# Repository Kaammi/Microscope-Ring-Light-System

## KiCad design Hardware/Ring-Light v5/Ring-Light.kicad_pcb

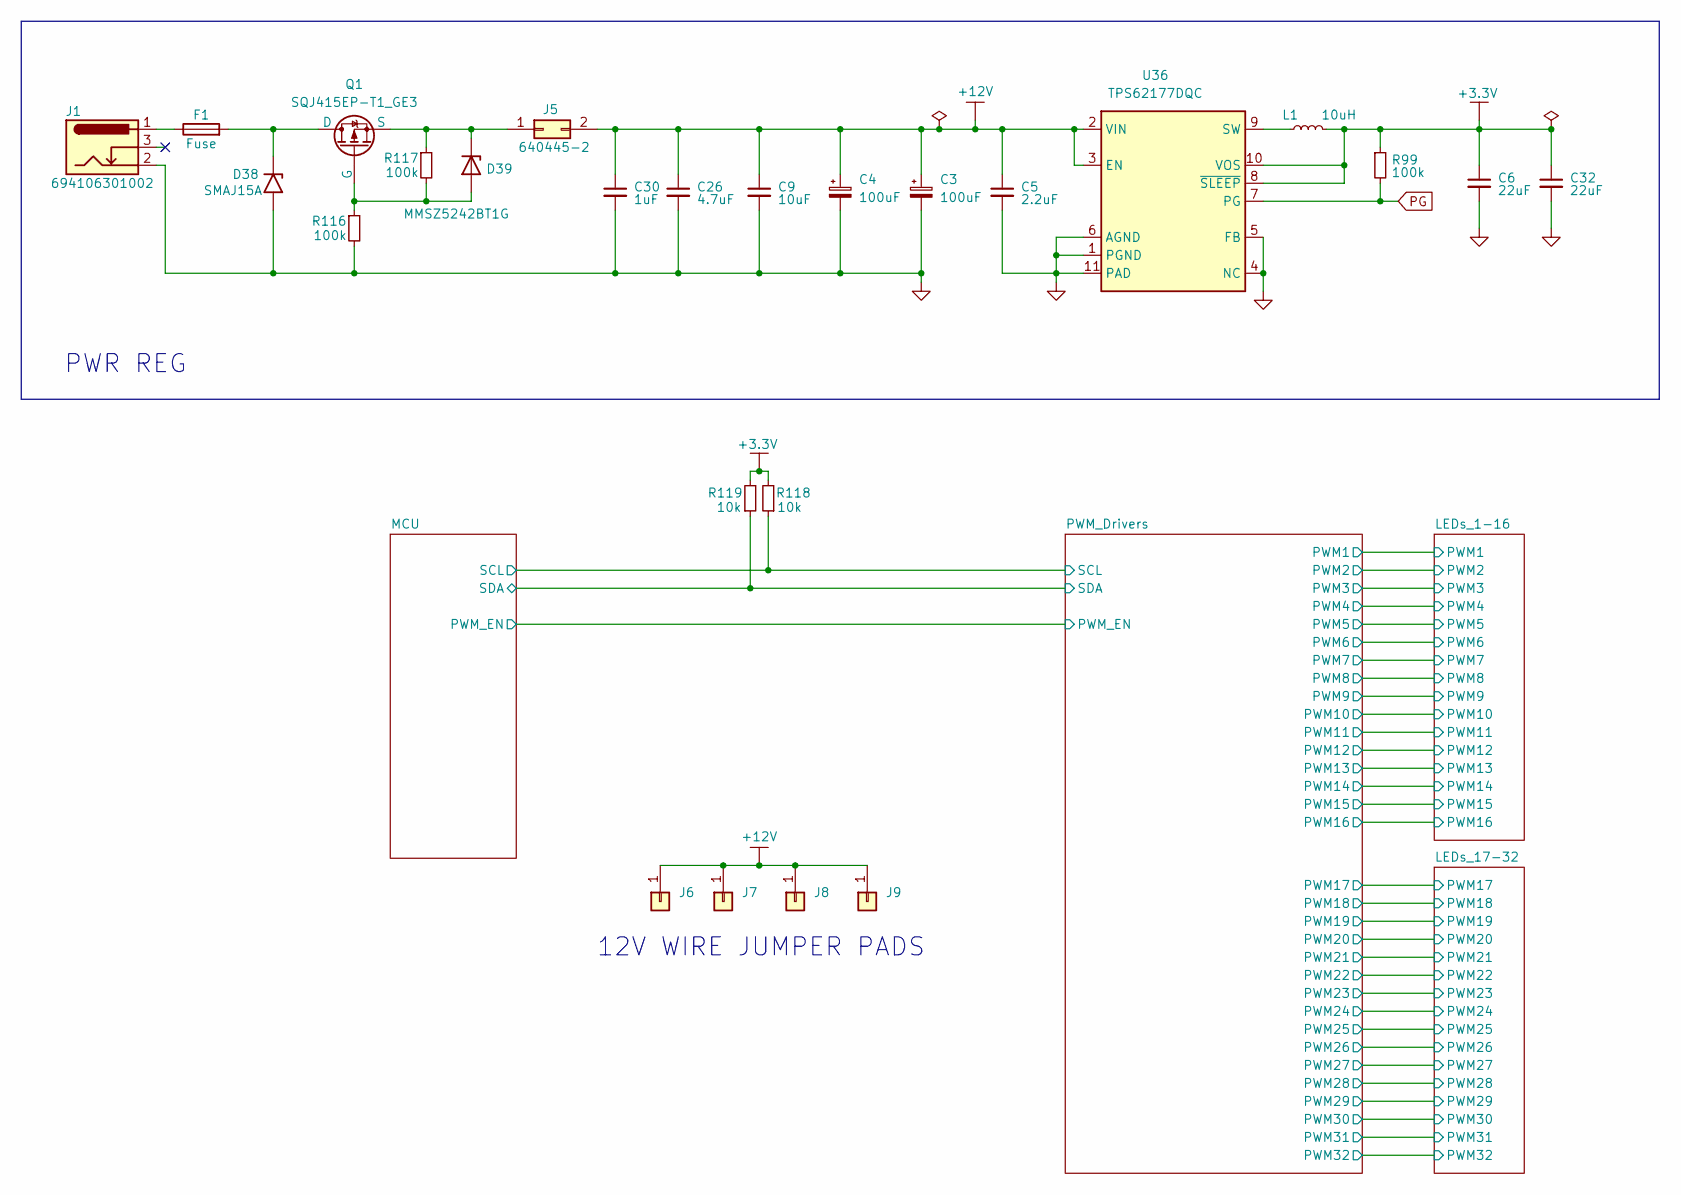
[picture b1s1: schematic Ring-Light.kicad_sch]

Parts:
C3, C4: 100uF
C5: 2.2uF; C_0805_2012Metric
C6, C32: 22uF; C_0805_2012Metric
C9: 10uF; C_0805_2012Metric
C26: 4.7uF; C_0805_2012Metric
C30: 1uF; C_0805_2012Metric
D38: SMAJ15A; D_SMA
D39: MMSZ5242BT1G; SOD3716X135N
F1: Fuse
J1: 694106301002
J5: 640445-2
J6, J7, J8, J9: Conn_01x01
L1: 10uH; WE-LHMI_4020
Q1: SQJ415EP-T1_GE3; SOT_SQJ415EP_VIS
R99, R116, R117: 100k; R_0402_1005Metric
R118, R119: 10k; R_0402_1005Metric
U36: TPS62177DQC; WSON-10-1EP_2x3mm_P0.5mm_EP0.84x2.4mm_ThermalVias

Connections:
+3.3V: C6.1, C32.1, L1.2, R99.1, R118.2, R119.2, U36.8 (~SLEEP), U36.10 (VOS); also elsewhere on the board
+12V: C3.1, C4.1, C5.1, C9.1, C26.1, C30.1, J5.2, J6.1 (Pin_1_1), J7.1 (Pin_1_1), J8.1 (Pin_1_1), J9.1 (Pin_1_1), U36.2 (VIN), U36.3 (EN); also elsewhere on the board
/MCU/SCL: R118.1; also elsewhere on the board
/MCU/SDA: R119.1; also elsewhere on the board
GND: C3.2, C4.2, C5.2, C6.2, C9.2, C26.2, C30.2, C32.2, D38.2 (A2), J1.2, R116.2, U36.1 (PGND), U36.4 (NC), U36.5 (FB), U36.6 (AGND), U36.11 (PAD); also elsewhere on the board
unnamed: D38.1 (A1), F1.2, Q1.5 (D)
unnamed: D39.2 (A), Q1.4 (G), R116.1, R117.2
unnamed: D39.1 (K), J5.1, Q1.1 (S), Q1.2 (S), Q1.3 (S), R117.1
unnamed: F1.1, J1.1
unnamed: L1.1, U36.9 (SW)
PG: R99.2, U36.7 (PG)

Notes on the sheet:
PWR REG
12V WIRE JUMPER PADS

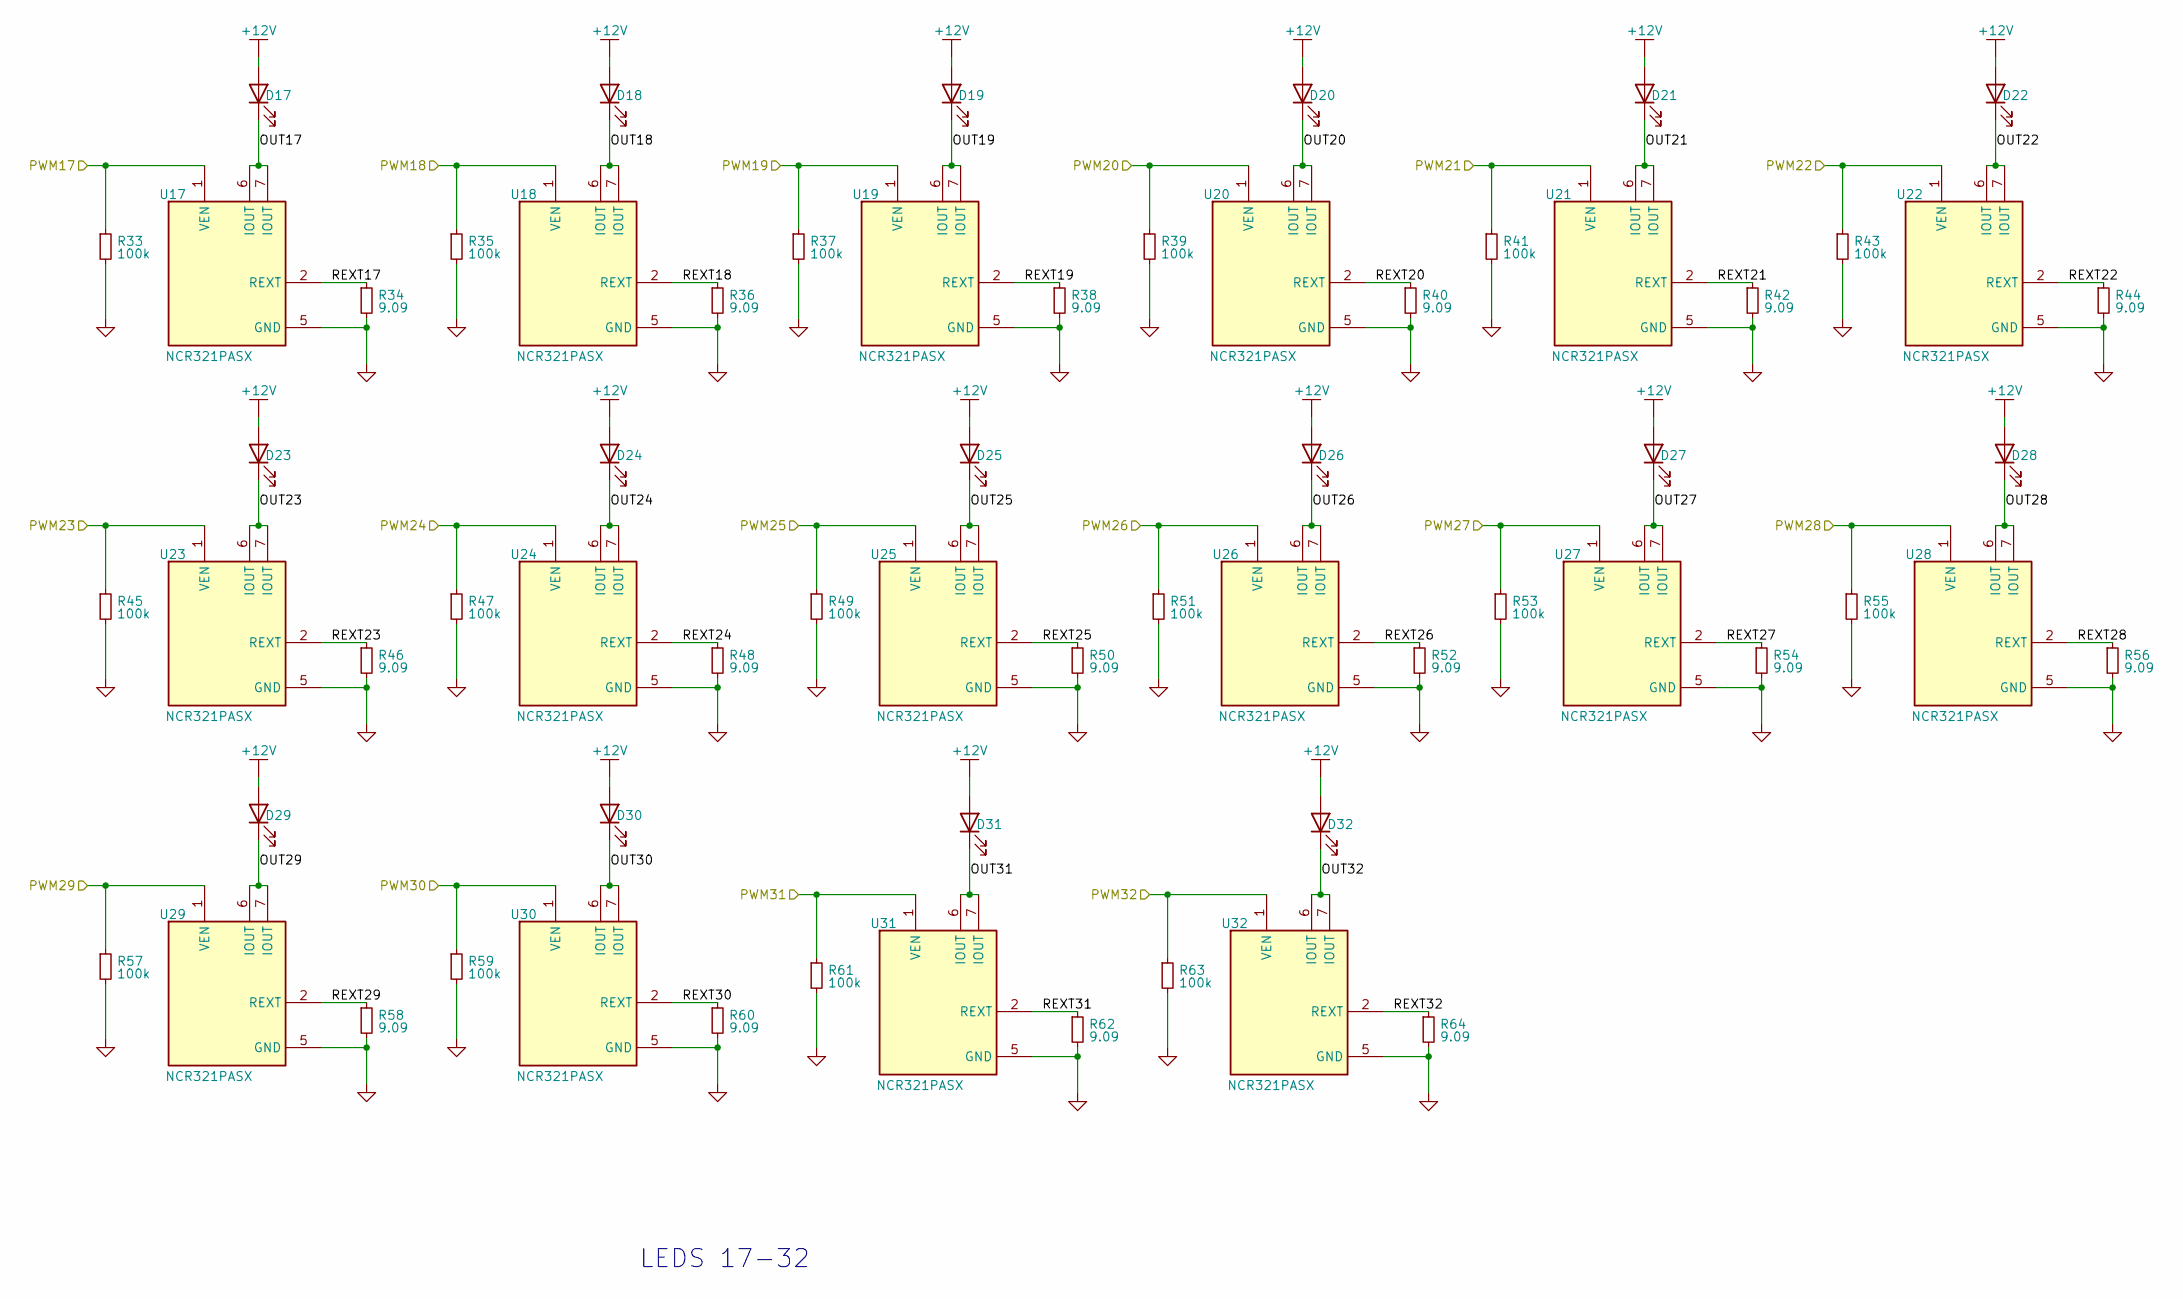
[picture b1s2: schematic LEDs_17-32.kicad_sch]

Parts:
D17, D18, D19, D20, D21, D22, D23, D24, D25, D26, D27, D28, D29, D30, D31, D32: LED; GWJTLRS1EMLVL5XX531
R33, R35, R37, R39, R41, R43, R45, R47, R49, R51, R53, R55, R57, R59, R61, R63: 100k; R_0402_1005Metric
R34, R36, R38, R40, R42, R44, R46, R48, R50, R52, R54, R56, R58, R60, R62, R64: 9.09; R_0402_1005Metric
U17, U18, U19, U20, U21, U22, U23, U24, U25, U26, U27, U28, U29, U30, U31, U32: NCR321PASX; Manufacturer_Part_Number NCR321PASX; Mouser Part Number 771-NCR321PASX

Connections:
+12V: D17.3 (A), D17.4 (A), D18.3 (A), D18.4 (A), D19.3 (A), D19.4 (A), D20.3 (A), D20.4 (A), D21.3 (A), D21.4 (A), D22.3 (A), D22.4 (A), D23.3 (A), D23.4 (A), D24.3 (A), D24.4 (A), D25.3 (A), D25.4 (A), D26.3 (A), D26.4 (A), D27.3 (A), D27.4 (A), D28.3 (A), D28.4 (A), D29.3 (A), D29.4 (A), D30.3 (A), D30.4 (A), D31.3 (A), D31.4 (A), D32.3 (A), D32.4 (A); also elsewhere on the board
/LEDs_17-32/OUT17: D17.1 (K), D17.2 (K), U17.6 (IOUT), U17.7 (IOUT)
/LEDs_17-32/OUT18: D18.1 (K), D18.2 (K), U18.6 (IOUT), U18.7 (IOUT)
/LEDs_17-32/OUT19: D19.1 (K), D19.2 (K), U19.6 (IOUT), U19.7 (IOUT)
/LEDs_17-32/OUT20: D20.1 (K), D20.2 (K), U20.6 (IOUT), U20.7 (IOUT)
/LEDs_17-32/OUT21: D21.1 (K), D21.2 (K), U21.6 (IOUT), U21.7 (IOUT)
/LEDs_17-32/OUT22: D22.1 (K), D22.2 (K), U22.6 (IOUT), U22.7 (IOUT)
/LEDs_17-32/OUT23: D23.1 (K), D23.2 (K), U23.6 (IOUT), U23.7 (IOUT)
/LEDs_17-32/OUT24: D24.1 (K), D24.2 (K), U24.6 (IOUT), U24.7 (IOUT)
/LEDs_17-32/OUT25: D25.1 (K), D25.2 (K), U25.6 (IOUT), U25.7 (IOUT)
/LEDs_17-32/OUT26: D26.1 (K), D26.2 (K), U26.6 (IOUT), U26.7 (IOUT)
/LEDs_17-32/OUT27: D27.1 (K), D27.2 (K), U27.6 (IOUT), U27.7 (IOUT)
/LEDs_17-32/OUT28: D28.1 (K), D28.2 (K), U28.6 (IOUT), U28.7 (IOUT)
/LEDs_17-32/OUT29: D29.1 (K), D29.2 (K), U29.6 (IOUT), U29.7 (IOUT)
/LEDs_17-32/OUT30: D30.1 (K), D30.2 (K), U30.6 (IOUT), U30.7 (IOUT)
/LEDs_17-32/OUT31: D31.1 (K), D31.2 (K), U31.6 (IOUT), U31.7 (IOUT)
/LEDs_17-32/OUT32: D32.1 (K), D32.2 (K), U32.6 (IOUT), U32.7 (IOUT)
/LEDs_17-32/PWM17: R33.1, U17.1 (VEN); also elsewhere on the board
/LEDs_17-32/PWM18: R35.1, U18.1 (VEN); also elsewhere on the board
/LEDs_17-32/PWM19: R37.1, U19.1 (VEN); also elsewhere on the board
/LEDs_17-32/PWM20: R39.1, U20.1 (VEN); also elsewhere on the board
/LEDs_17-32/PWM21: R41.1, U21.1 (VEN); also elsewhere on the board
/LEDs_17-32/PWM22: R43.1, U22.1 (VEN); also elsewhere on the board
/LEDs_17-32/PWM23: R45.1, U23.1 (VEN); also elsewhere on the board
/LEDs_17-32/PWM24: R47.1, U24.1 (VEN); also elsewhere on the board
/LEDs_17-32/PWM25: R49.1, U25.1 (VEN); also elsewhere on the board
/LEDs_17-32/PWM26: R51.1, U26.1 (VEN); also elsewhere on the board
/LEDs_17-32/PWM27: R53.1, U27.1 (VEN); also elsewhere on the board
/LEDs_17-32/PWM28: R55.1, U28.1 (VEN); also elsewhere on the board
/LEDs_17-32/PWM29: R57.1, U29.1 (VEN); also elsewhere on the board
/LEDs_17-32/PWM30: R59.1, U30.1 (VEN); also elsewhere on the board
/LEDs_17-32/PWM31: R61.1, U31.1 (VEN); also elsewhere on the board
/LEDs_17-32/PWM32: R63.1, U32.1 (VEN); also elsewhere on the board
/LEDs_17-32/REXT17: R34.1, U17.2 (REXT)
/LEDs_17-32/REXT18: R36.1, U18.2 (REXT)
/LEDs_17-32/REXT19: R38.1, U19.2 (REXT)
/LEDs_17-32/REXT20: R40.1, U20.2 (REXT)
/LEDs_17-32/REXT21: R42.1, U21.2 (REXT)
/LEDs_17-32/REXT22: R44.1, U22.2 (REXT)
/LEDs_17-32/REXT23: R46.1, U23.2 (REXT)
/LEDs_17-32/REXT24: R48.1, U24.2 (REXT)
/LEDs_17-32/REXT25: R50.1, U25.2 (REXT)
/LEDs_17-32/REXT26: R52.1, U26.2 (REXT)
/LEDs_17-32/REXT27: R54.1, U27.2 (REXT)
/LEDs_17-32/REXT28: R56.1, U28.2 (REXT)
/LEDs_17-32/REXT29: R58.1, U29.2 (REXT)
/LEDs_17-32/REXT30: R60.1, U30.2 (REXT)
/LEDs_17-32/REXT31: R62.1, U31.2 (REXT)
/LEDs_17-32/REXT32: R64.1, U32.2 (REXT)
GND: R33.2, R34.2, R35.2, R36.2, R37.2, R38.2, R39.2, R40.2, R41.2, R42.2, R43.2, R44.2, R45.2, R46.2, R47.2, R48.2, R49.2, R50.2, R51.2, R52.2, R53.2, R54.2, R55.2, R56.2, R57.2, R58.2, R59.2, R60.2, R61.2, R62.2, R63.2, R64.2, U17.5 (GND), U18.5 (GND), U19.5 (GND), U20.5 (GND), U21.5 (GND), U22.5 (GND), U23.5 (GND), U24.5 (GND), U25.5 (GND), U26.5 (GND), U27.5 (GND), U28.5 (GND), U29.5 (GND), U30.5 (GND), U31.5 (GND), U32.5 (GND); also elsewhere on the board

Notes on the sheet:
LEDS 17-32

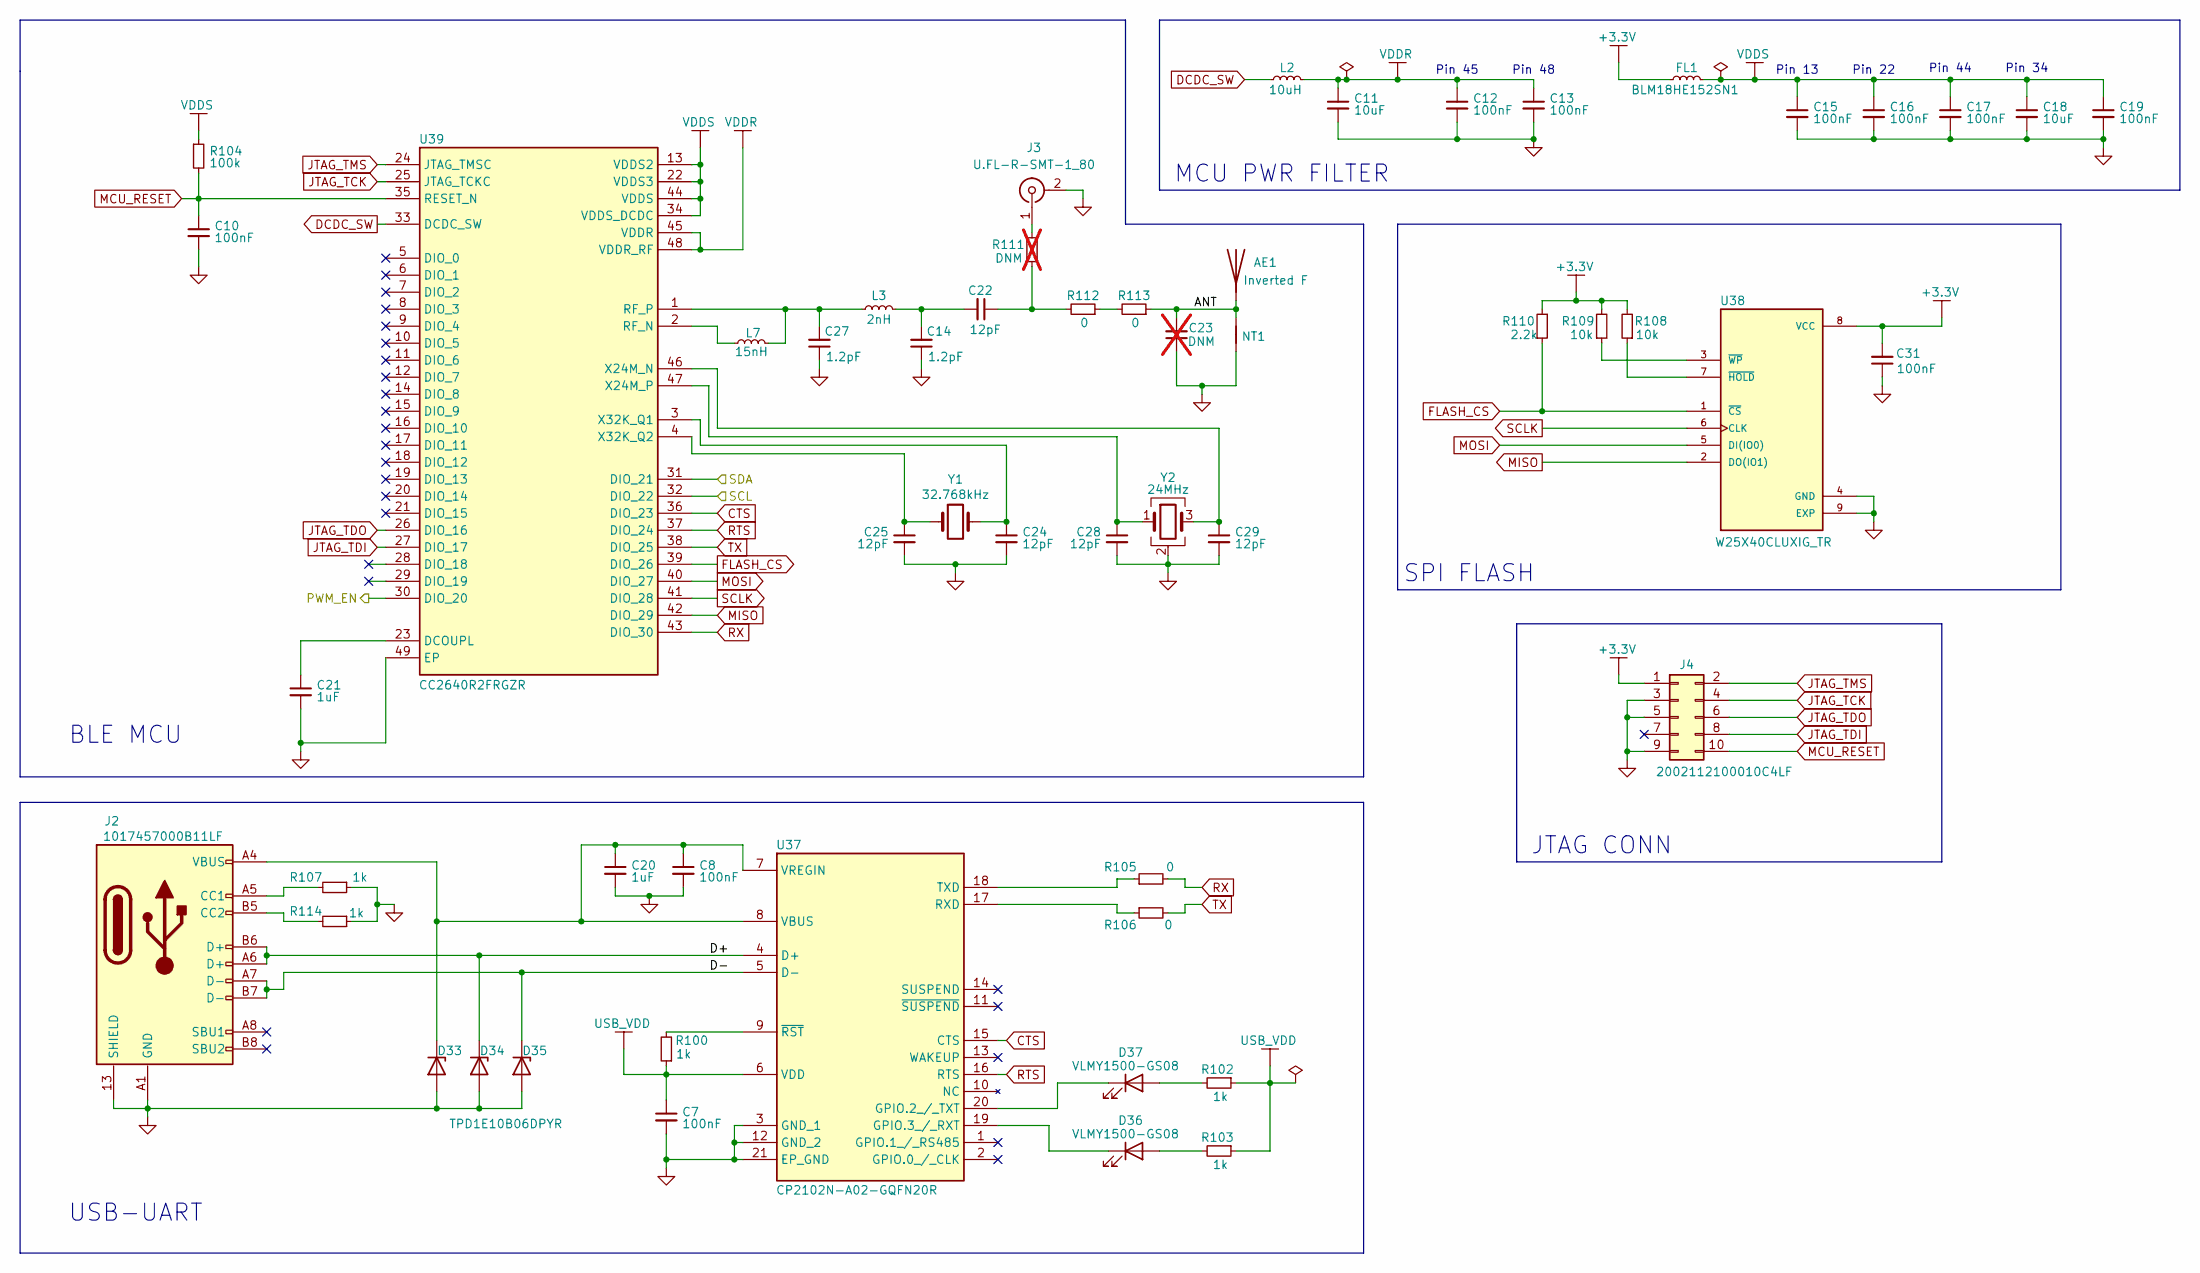
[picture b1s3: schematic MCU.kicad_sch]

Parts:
AE1: Inverted F
C7, C8, C10, C12, C13, C15, C16, C17, C19, C31: 100nF; C_0402_1005Metric
C11, C18: 10uF; C_0402_1005Metric
C14, C27: 1.2pF; C_0402_1005Metric
C20, C21: 1uF; C_0402_1005Metric
C22, C24, C25, C28, C29: 12pF; C_0402_1005Metric
C23: DNM; C_0402_1005Metric; not fitted
D33, D34, D35: TPD1E10B06DPYR; D_SOD-523
D36, D37: VLMY1500-GS08; LED_0402_1005Metric
FL1: BLM18HE152SN1; L_0603_1608Metric
J2: 1017457000B11LF
J3: U.FL-R-SMT-1_80; UFLRSMT180
J4: 2002112100010C4LF
L2: 10uH; L_0805_2012Metric
L3: 2nH
L7: 15nH
NT1: NetTie_2
R100, R102, R103, R107, R114: 1k; R_0402_1005Metric
R104: 100k; R_0402_1005Metric
R105, R106, R112, R113: 0; R_0402_1005Metric
R108, R109: 10k; R_0402_1005Metric
R110: 2.2k; R_0402_1005Metric
R111: DNM; R_0402_1005Metric; not fitted
U37: CP2102N-A02-GQFN20R; CP2102NA02GQFN20; Manufacturer_Part_Number CP2102N-A02-GQFN20R; Mouser Part Number 634-CP2102NA02QFN20R
U38: W25X40CLUXIG_TR; PSON50P300X200X60-9N; PARTREV F
U39: CC2640R2FRGZR; QFN50P700X700X100-49N-D; Manufacturer_Part_Number CC2640R2FRGZR; Mouser Part Number 595-CC2640R2FRGZR
Y1: 32.768kHz; FC135327680KAAG0
Y2: 24MHz; TSX-3225

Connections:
+3.3V: C31.2, FL1.1, J4.1, R108.2, R109.2, R110.2, U38.8 (VCC); also elsewhere on the board
/MCU/<NO NET>: C8.1, C20.1, D33.1 (K), J2.A4 (VBUS), J2.B4 (VBUS), U37.7 (VREGIN), U37.8 (VBUS)
/MCU/ANT: AE1.1, C23.2, NT1.2, R113.1
/MCU/D+: D34.1 (K), J2.A6 (D+), J2.B6 (D+), U37.4 (D+)
/MCU/D-: D35.1 (K), J2.A7 (D-), J2.B7 (D-), U37.5 (D-)
/MCU/PWM_EN: U39.30 (DIO_20); also elsewhere on the board
/MCU/SCL: U39.32 (DIO_22); also elsewhere on the board
/MCU/SDA: U39.31 (DIO_21); also elsewhere on the board
CTS: U37.15 (CTS), U39.36 (DIO_23)
DCDC_SW: L2.1, U39.33 (DCDC_SW)
FLASH_CS: R110.1, U38.1 (~CS), U39.39 (DIO_26)
GND: C7.2, C8.2, C10.2, C11.2, C12.2, C13.2, C14.1, C15.2, C16.2, C17.2, C18.2, C19.2, C20.2, C21.2, C23.1, C24.2, C25.2, C27.1, C28.2, C29.2, C31.1, D33.2 (A), D34.2 (A), D35.2 (A), J2.13 (SHIELD), J2.14 (SHIELD), J2.15 (SHIELD), J2.16 (SHIELD), J2.A1 (GND), J2.B1 (GND), J3.2 (Ext), J3.3 (Ext), J4.3, J4.5, J4.9, NT1.1, R107.1, R114.1, U37.3 (GND_1), U37.12 (GND_2), U37.21 (EP_GND), U38.4 (GND), U38.9 (EXP), U39.49 (EP), Y2.2 (G), Y2.4 (G); also elsewhere on the board
JTAG_TCK: J4.4, U39.25 (JTAG_TCKC)
JTAG_TDI: J4.8, U39.27 (DIO_17)
JTAG_TDO: J4.6, U39.26 (DIO_16)
JTAG_TMS: J4.2, U39.24 (JTAG_TMSC)
MCU_RESET: C10.1, J4.10, R104.2, U39.35 (RESET_N)
MISO: U38.2 (DO(IO1)), U39.42 (DIO_29)
MOSI: U38.5 (DI(IO0)), U39.40 (DIO_27)
unnamed: C14.2, C22.2, L3.2
unnamed: C22.1, R111.1, R112.2
unnamed: D36.2 (A), R103.2
unnamed: D36.1 (K), U37.19 (GPIO.3_/_RXT)
unnamed: D37.2 (A), R102.2
unnamed: D37.1 (K), U37.20 (GPIO.2_/_TXT)
unnamed: J2.A5 (CC1), R107.2
unnamed: J2.B5 (CC2), R114.2
unnamed: J3.1 (In), R111.2
unnamed: R112.1, R113.2
unnamed: R106.1, U37.17 (RXD)
unnamed: R105.1, U37.18 (TXD)
unnamed: R100.2, U37.9 (~RST)
unnamed: R108.1, U38.7 (~HOLD)
unnamed: R109.1, U38.3 (~WP)
unnamed: C21.1, U39.23 (DCOUPL)
unnamed: L7.1, U39.2 (RF_N)
unnamed: C27.2, L3.1, L7.2, U39.1 (RF_P)
unnamed: C29.1, U39.46 (X24M_N), Y2.3
unnamed: C28.1, U39.47 (X24M_P), Y2.1
unnamed: C24.1, U39.3 (X32K_Q1), Y1.2
unnamed: C25.1, U39.4 (X32K_Q2), Y1.1
RTS: U37.16 (RTS), U39.37 (DIO_24)
RX: R105.2, U39.43 (DIO_30)
SCLK: U38.6 (CLK), U39.41 (DIO_28)
TX: R106.2, U39.38 (DIO_25)
USB_VDD: C7.1, R100.1, R102.1, R103.1, U37.6 (VDD)
VDDR: C11.1, C12.1, C13.1, L2.2, U39.45 (VDDR), U39.48 (VDDR_RF)
VDDS: C15.1, C16.1, C17.1, C18.1, C19.1, FL1.2, R104.1, U39.13 (VDDS2), U39.22 (VDDS3), U39.34 (VDDS_DCDC), U39.44 (VDDS)

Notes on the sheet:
Pin 44
JTAG CONN
Pin 22
Pin 45
SPI FLASH
Pin 13
Pin 34
USB-UART
MCU PWR FILTER
BLE MCU
Pin 48

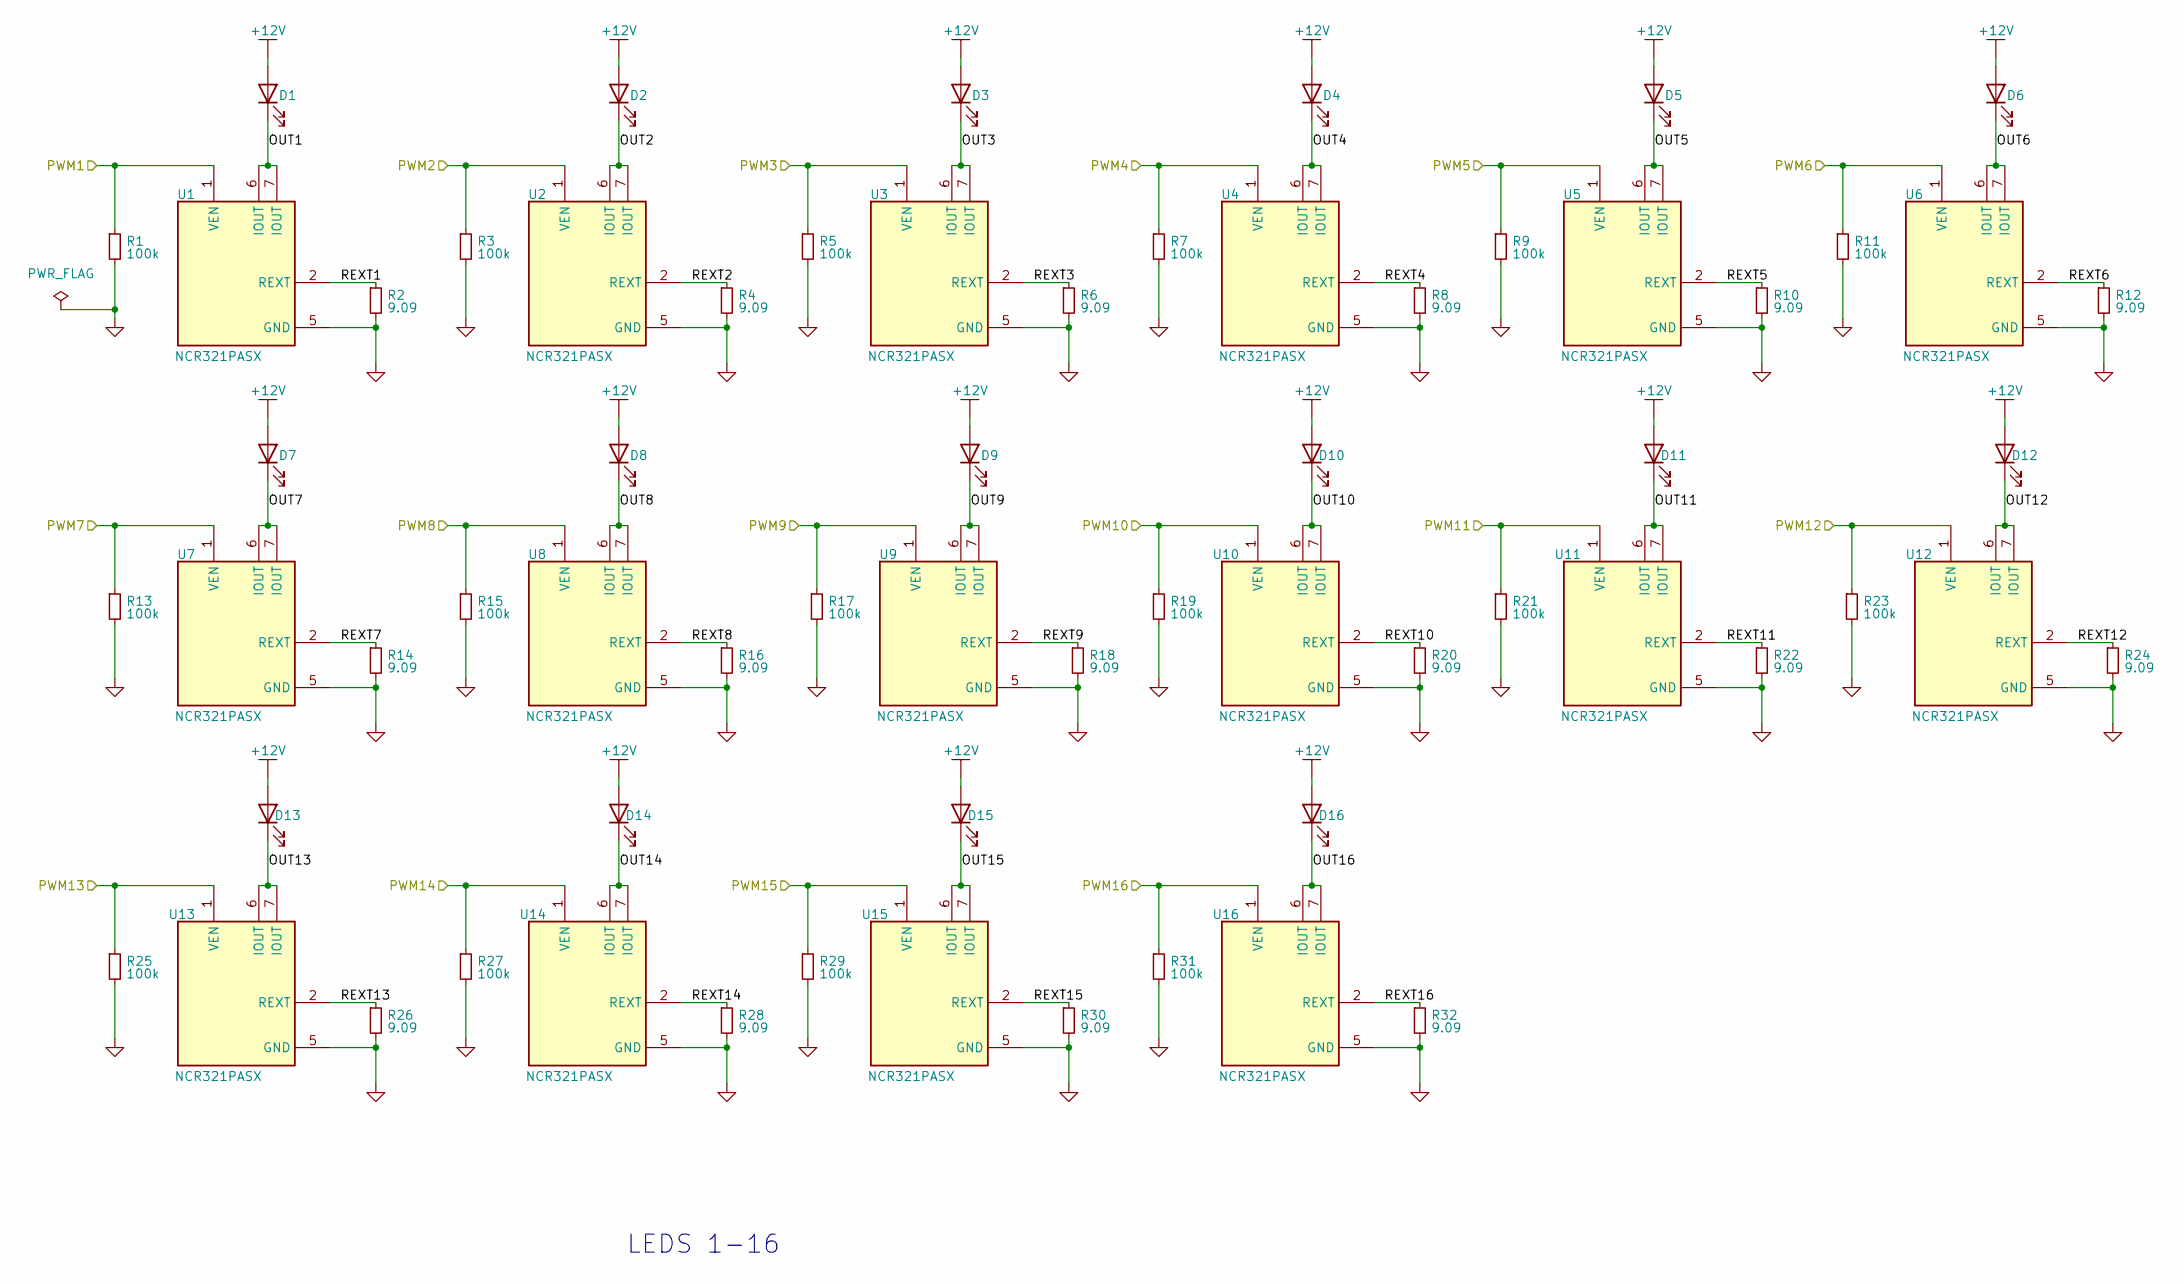
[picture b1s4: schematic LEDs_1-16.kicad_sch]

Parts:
D1, D2, D3, D4, D5, D6, D7, D8, D9, D10, D11, D12, D13, D14, D15, D16: LED; GWJTLRS1EMLVL5XX531
R1, R3, R5, R7, R9, R11, R13, R15, R17, R19, R21, R23, R25, R27, R29, R31: 100k; R_0402_1005Metric
R2, R4, R6, R8, R10, R12, R14, R16, R18, R20, R22, R24, R26, R28, R30, R32: 9.09; R_0402_1005Metric
U1, U2, U3, U4, U5, U6, U7, U8, U9, U10, U11, U12, U13, U14, U15, U16: NCR321PASX; Manufacturer_Part_Number NCR321PASX; Mouser Part Number 771-NCR321PASX

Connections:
+12V: D1.3 (A), D1.4 (A), D2.3 (A), D2.4 (A), D3.3 (A), D3.4 (A), D4.3 (A), D4.4 (A), D5.3 (A), D5.4 (A), D6.3 (A), D6.4 (A), D7.3 (A), D7.4 (A), D8.3 (A), D8.4 (A), D9.3 (A), D9.4 (A), D10.3 (A), D10.4 (A), D11.3 (A), D11.4 (A), D12.3 (A), D12.4 (A), D13.3 (A), D13.4 (A), D14.3 (A), D14.4 (A), D15.3 (A), D15.4 (A), D16.3 (A), D16.4 (A); also elsewhere on the board
/LEDs_1-16/OUT1: D1.1 (K), D1.2 (K), U1.6 (IOUT), U1.7 (IOUT)
/LEDs_1-16/OUT2: D2.1 (K), D2.2 (K), U2.6 (IOUT), U2.7 (IOUT)
/LEDs_1-16/OUT3: D3.1 (K), D3.2 (K), U3.6 (IOUT), U3.7 (IOUT)
/LEDs_1-16/OUT4: D4.1 (K), D4.2 (K), U4.6 (IOUT), U4.7 (IOUT)
/LEDs_1-16/OUT5: D5.1 (K), D5.2 (K), U5.6 (IOUT), U5.7 (IOUT)
/LEDs_1-16/OUT6: D6.1 (K), D6.2 (K), U6.6 (IOUT), U6.7 (IOUT)
/LEDs_1-16/OUT7: D7.1 (K), D7.2 (K), U7.6 (IOUT), U7.7 (IOUT)
/LEDs_1-16/OUT8: D8.1 (K), D8.2 (K), U8.6 (IOUT), U8.7 (IOUT)
/LEDs_1-16/OUT9: D9.1 (K), D9.2 (K), U9.6 (IOUT), U9.7 (IOUT)
/LEDs_1-16/OUT10: D10.1 (K), D10.2 (K), U10.6 (IOUT), U10.7 (IOUT)
/LEDs_1-16/OUT11: D11.1 (K), D11.2 (K), U11.6 (IOUT), U11.7 (IOUT)
/LEDs_1-16/OUT12: D12.1 (K), D12.2 (K), U12.6 (IOUT), U12.7 (IOUT)
/LEDs_1-16/OUT13: D13.1 (K), D13.2 (K), U13.6 (IOUT), U13.7 (IOUT)
/LEDs_1-16/OUT14: D14.1 (K), D14.2 (K), U14.6 (IOUT), U14.7 (IOUT)
/LEDs_1-16/OUT15: D15.1 (K), D15.2 (K), U15.6 (IOUT), U15.7 (IOUT)
/LEDs_1-16/OUT16: D16.1 (K), D16.2 (K), U16.6 (IOUT), U16.7 (IOUT)
/LEDs_1-16/PWM1: R1.1, U1.1 (VEN); also elsewhere on the board
/LEDs_1-16/PWM2: R3.1, U2.1 (VEN); also elsewhere on the board
/LEDs_1-16/PWM3: R5.1, U3.1 (VEN); also elsewhere on the board
/LEDs_1-16/PWM4: R7.1, U4.1 (VEN); also elsewhere on the board
/LEDs_1-16/PWM5: R9.1, U5.1 (VEN); also elsewhere on the board
/LEDs_1-16/PWM6: R11.1, U6.1 (VEN); also elsewhere on the board
/LEDs_1-16/PWM7: R13.1, U7.1 (VEN); also elsewhere on the board
/LEDs_1-16/PWM8: R15.1, U8.1 (VEN); also elsewhere on the board
/LEDs_1-16/PWM9: R17.1, U9.1 (VEN); also elsewhere on the board
/LEDs_1-16/PWM10: R19.1, U10.1 (VEN); also elsewhere on the board
/LEDs_1-16/PWM11: R21.1, U11.1 (VEN); also elsewhere on the board
/LEDs_1-16/PWM12: R23.1, U12.1 (VEN); also elsewhere on the board
/LEDs_1-16/PWM13: R25.1, U13.1 (VEN); also elsewhere on the board
/LEDs_1-16/PWM14: R27.1, U14.1 (VEN); also elsewhere on the board
/LEDs_1-16/PWM15: R29.1, U15.1 (VEN); also elsewhere on the board
/LEDs_1-16/PWM16: R31.1, U16.1 (VEN); also elsewhere on the board
/LEDs_1-16/REXT1: R2.1, U1.2 (REXT)
/LEDs_1-16/REXT2: R4.1, U2.2 (REXT)
/LEDs_1-16/REXT3: R6.1, U3.2 (REXT)
/LEDs_1-16/REXT4: R8.1, U4.2 (REXT)
/LEDs_1-16/REXT5: R10.1, U5.2 (REXT)
/LEDs_1-16/REXT6: R12.1, U6.2 (REXT)
/LEDs_1-16/REXT7: R14.1, U7.2 (REXT)
/LEDs_1-16/REXT8: R16.1, U8.2 (REXT)
/LEDs_1-16/REXT9: R18.1, U9.2 (REXT)
/LEDs_1-16/REXT10: R20.1, U10.2 (REXT)
/LEDs_1-16/REXT11: R22.1, U11.2 (REXT)
/LEDs_1-16/REXT12: R24.1, U12.2 (REXT)
/LEDs_1-16/REXT13: R26.1, U13.2 (REXT)
/LEDs_1-16/REXT14: R28.1, U14.2 (REXT)
/LEDs_1-16/REXT15: R30.1, U15.2 (REXT)
/LEDs_1-16/REXT16: R32.1, U16.2 (REXT)
GND: R1.2, R2.2, R3.2, R4.2, R5.2, R6.2, R7.2, R8.2, R9.2, R10.2, R11.2, R12.2, R13.2, R14.2, R15.2, R16.2, R17.2, R18.2, R19.2, R20.2, R21.2, R22.2, R23.2, R24.2, R25.2, R26.2, R27.2, R28.2, R29.2, R30.2, R31.2, R32.2, U1.5 (GND), U2.5 (GND), U3.5 (GND), U4.5 (GND), U5.5 (GND), U6.5 (GND), U7.5 (GND), U8.5 (GND), U9.5 (GND), U10.5 (GND), U11.5 (GND), U12.5 (GND), U13.5 (GND), U14.5 (GND), U15.5 (GND), U16.5 (GND); also elsewhere on the board

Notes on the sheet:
LEDS 1-16

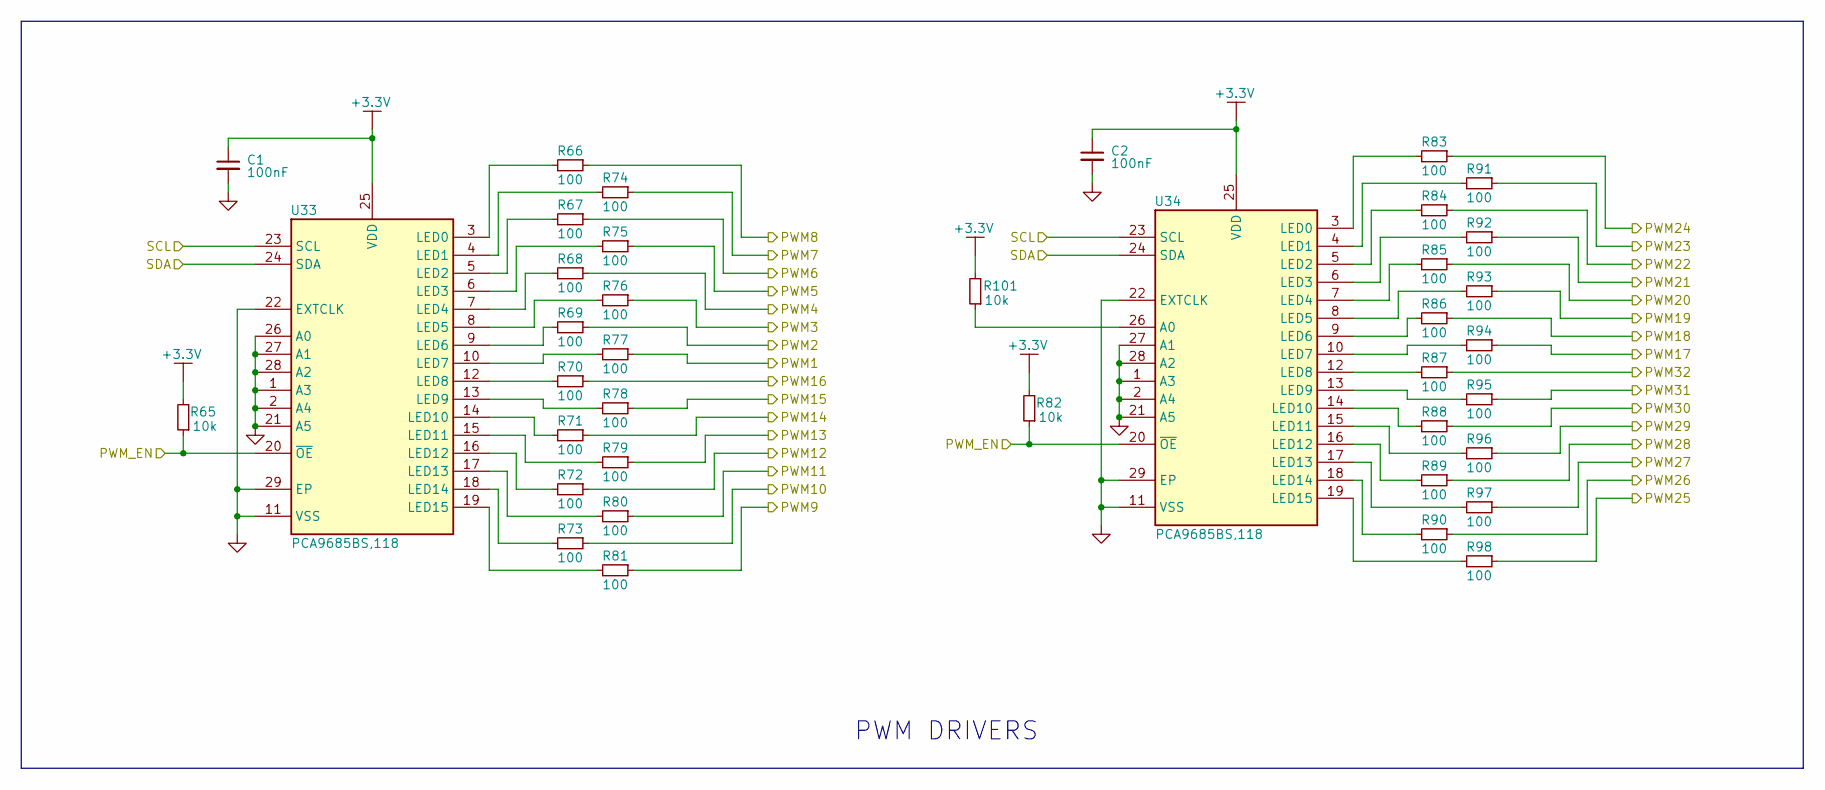
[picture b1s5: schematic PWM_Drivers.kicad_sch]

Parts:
C1, C2: 100nF; C_0402_1005Metric
R65, R82, R101: 10k; R_0402_1005Metric
R66, R67, R68, R69, R70, R71, R72, R73, R74, R75, R76, R77, R78, R79, R80, R81, R83, R84, R85, R86, R87, R88, R89, R90, R91, R92, R93, R94, R95, R96, R97, R98: 100; R_0402_1005Metric
U33, U34: PCA9685BS,118; QFN65P600X600X100-29N-D; Manufacturer_Part_Number PCA9685BS,118; Mouser Part Number 771-PCA9685BS118

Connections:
+3.3V: C1.1, C2.1, R65.2, R82.2, R101.2, U33.25 (VDD), U34.25 (VDD); also elsewhere on the board
/LEDs_1-16/PWM1: R77.1; also elsewhere on the board
/LEDs_1-16/PWM2: R69.1; also elsewhere on the board
/LEDs_1-16/PWM3: R76.1; also elsewhere on the board
/LEDs_1-16/PWM4: R68.1; also elsewhere on the board
/LEDs_1-16/PWM5: R75.1; also elsewhere on the board
/LEDs_1-16/PWM6: R67.1; also elsewhere on the board
/LEDs_1-16/PWM7: R74.1; also elsewhere on the board
/LEDs_1-16/PWM8: R66.1; also elsewhere on the board
/LEDs_1-16/PWM9: R81.1; also elsewhere on the board
/LEDs_1-16/PWM10: R73.1; also elsewhere on the board
/LEDs_1-16/PWM11: R80.1; also elsewhere on the board
/LEDs_1-16/PWM12: R72.1; also elsewhere on the board
/LEDs_1-16/PWM13: R79.1; also elsewhere on the board
/LEDs_1-16/PWM14: R71.1; also elsewhere on the board
/LEDs_1-16/PWM15: R78.1; also elsewhere on the board
/LEDs_1-16/PWM16: R70.1; also elsewhere on the board
/LEDs_17-32/PWM17: R94.1; also elsewhere on the board
/LEDs_17-32/PWM18: R86.1; also elsewhere on the board
/LEDs_17-32/PWM19: R93.1; also elsewhere on the board
/LEDs_17-32/PWM20: R85.1; also elsewhere on the board
/LEDs_17-32/PWM21: R92.1; also elsewhere on the board
/LEDs_17-32/PWM22: R84.1; also elsewhere on the board
/LEDs_17-32/PWM23: R91.1; also elsewhere on the board
/LEDs_17-32/PWM24: R83.1; also elsewhere on the board
/LEDs_17-32/PWM25: R98.1; also elsewhere on the board
/LEDs_17-32/PWM26: R90.1; also elsewhere on the board
/LEDs_17-32/PWM27: R97.1; also elsewhere on the board
/LEDs_17-32/PWM28: R89.1; also elsewhere on the board
/LEDs_17-32/PWM29: R96.1; also elsewhere on the board
/LEDs_17-32/PWM30: R88.1; also elsewhere on the board
/LEDs_17-32/PWM31: R95.1; also elsewhere on the board
/LEDs_17-32/PWM32: R87.1; also elsewhere on the board
/MCU/PWM_EN: R65.1, R82.1, U33.20 (~OE), U34.20 (~OE); also elsewhere on the board
/MCU/SCL: U33.23 (SCL), U34.23 (SCL); also elsewhere on the board
/MCU/SDA: U33.24 (SDA), U34.24 (SDA); also elsewhere on the board
GND: C1.2, C2.2, U33.1 (A3), U33.2 (A4), U33.11 (VSS), U33.21 (A5), U33.22 (EXTCLK), U33.26 (A0), U33.27 (A1), U33.28 (A2), U33.29 (EP), U34.1 (A3), U34.2 (A4), U34.11 (VSS), U34.21 (A5), U34.22 (EXTCLK), U34.27 (A1), U34.28 (A2), U34.29 (EP); also elsewhere on the board
unnamed: R66.2, U33.3 (LED0)
unnamed: R74.2, U33.4 (LED1)
unnamed: R67.2, U33.5 (LED2)
unnamed: R75.2, U33.6 (LED3)
unnamed: R68.2, U33.7 (LED4)
unnamed: R76.2, U33.8 (LED5)
unnamed: R69.2, U33.9 (LED6)
unnamed: R77.2, U33.10 (LED7)
unnamed: R70.2, U33.12 (LED8)
unnamed: R78.2, U33.13 (LED9)
unnamed: R71.2, U33.14 (LED10)
unnamed: R79.2, U33.15 (LED11)
unnamed: R72.2, U33.16 (LED12)
unnamed: R80.2, U33.17 (LED13)
unnamed: R73.2, U33.18 (LED14)
unnamed: R81.2, U33.19 (LED15)
unnamed: R101.1, U34.26 (A0)
unnamed: R83.2, U34.3 (LED0)
unnamed: R91.2, U34.4 (LED1)
unnamed: R84.2, U34.5 (LED2)
unnamed: R92.2, U34.6 (LED3)
unnamed: R85.2, U34.7 (LED4)
unnamed: R93.2, U34.8 (LED5)
unnamed: R86.2, U34.9 (LED6)
unnamed: R94.2, U34.10 (LED7)
unnamed: R87.2, U34.12 (LED8)
unnamed: R95.2, U34.13 (LED9)
unnamed: R88.2, U34.14 (LED10)
unnamed: R96.2, U34.15 (LED11)
unnamed: R89.2, U34.16 (LED12)
unnamed: R97.2, U34.17 (LED13)
unnamed: R90.2, U34.18 (LED14)
unnamed: R98.2, U34.19 (LED15)

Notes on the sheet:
PWM DRIVERS
